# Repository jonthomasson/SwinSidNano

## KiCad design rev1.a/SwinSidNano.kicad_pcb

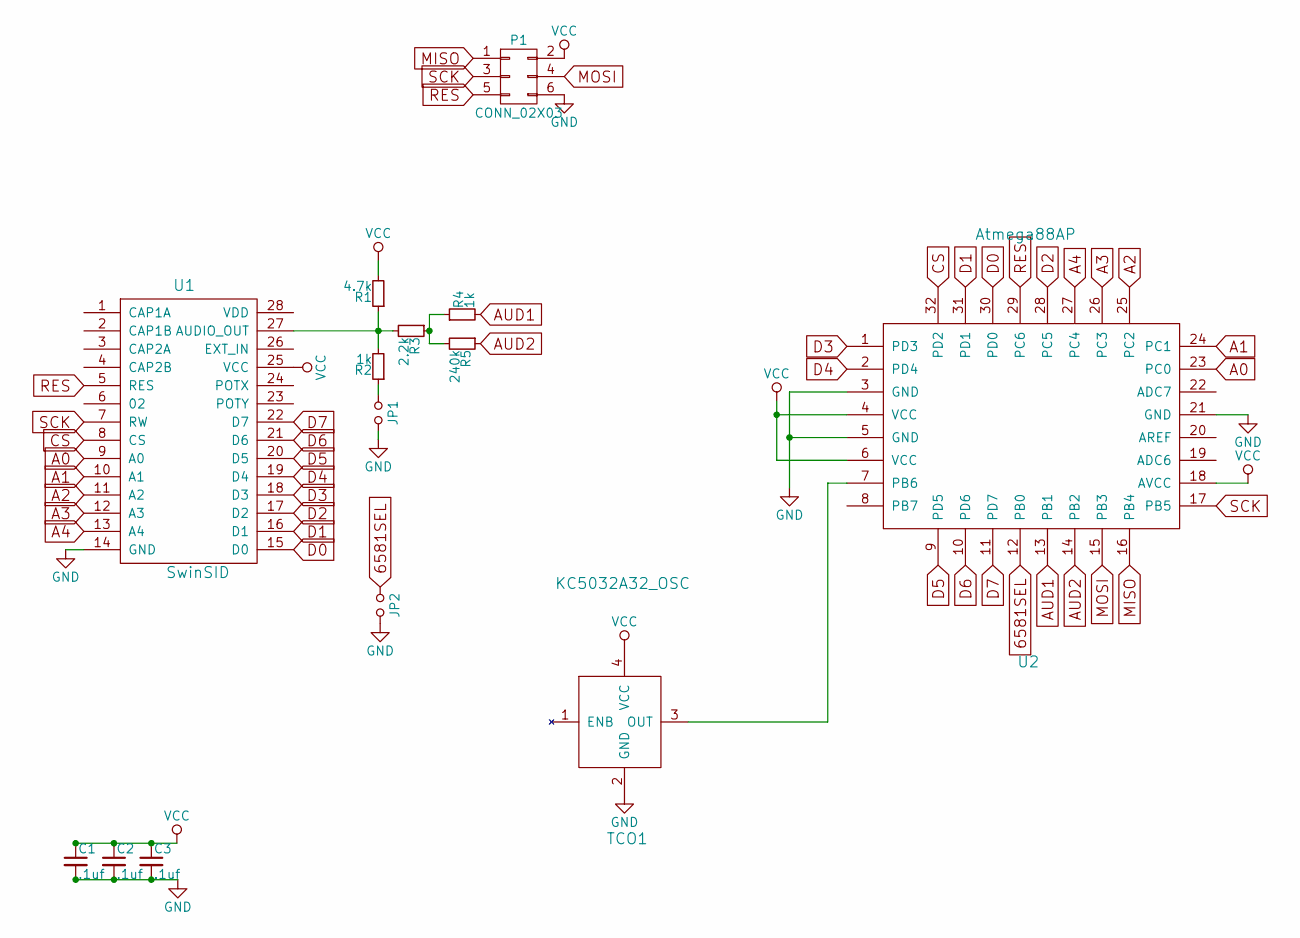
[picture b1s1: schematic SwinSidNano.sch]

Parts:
C1, C2, C3: .1uf; C_0805
JP1, JP2: Jumper_NO_Small; Pin_Header_Straight_1x02
P1: CONN_02X03; Pin_Header_Straight_2x03
R1: 4.7k; R_0805
R2, R4: 1k; R_0805
R3: 2.2k; R_0805
R5: 240k; R_0805
TCO1: KC5032A32_OSC; TCO-4
U1: SwinSID; DIP-28_W15.24mm
U2: Atmega88AP; TQFP-32_7x7mm_Pitch0.8mm

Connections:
6581SEL: JP2.1, U2.12 (PB0)
A0: U1.9 (A0), U2.23 (PC0)
A1: U1.10 (A1), U2.24 (PC1)
A2: U1.11 (A2), U2.25 (PC2)
A3: U1.12 (A3), U2.26 (PC3)
A4: U1.13 (A4), U2.27 (PC4)
AUD1: R4.2, U2.13 (PB1)
AUD2: R5.1, U2.14 (PB2)
CS: U1.8 (CS), U2.32 (PD2)
D0: U1.15 (D0), U2.30 (PD0)
D1: U1.16 (D1), U2.31 (PD1)
D2: U1.17 (D2), U2.28 (PC5)
D3: U1.18 (D3), U2.1 (PD3)
D4: U1.19 (D4), U2.2 (PD4)
D5: U1.20 (D5), U2.9 (PD5)
D6: U1.21 (D6), U2.10 (PD6)
D7: U1.22 (D7), U2.11 (PD7)
GND: C1.2, C2.2, C3.2, JP1.2, JP2.2, P1.6, TCO1.2 (GND), U1.14 (GND), U2.3 (GND), U2.5 (GND), U2.21 (GND); also elsewhere on the board
MISO: P1.1, U2.16 (PB4)
MOSI: P1.4, U2.15 (PB3)
unnamed: JP1.1, R2.1
unnamed: R1.1, R2.2, R3.2, U1.27 (AUDIO_OUT)
unnamed: R3.1, R4.1, R5.2
unnamed: TCO1.3 (OUT), U2.7 (PB6)
RES: P1.5, U1.5 (RES), U2.29 (PC6)
SCK: P1.3, U1.7 (RW), U2.17 (PB5)
VCC: C1.1, C2.1, C3.1, P1.2, R1.2, TCO1.4 (VCC), U1.25 (VCC), U2.4 (VCC), U2.6 (VCC), U2.18 (AVCC); also elsewhere on the board

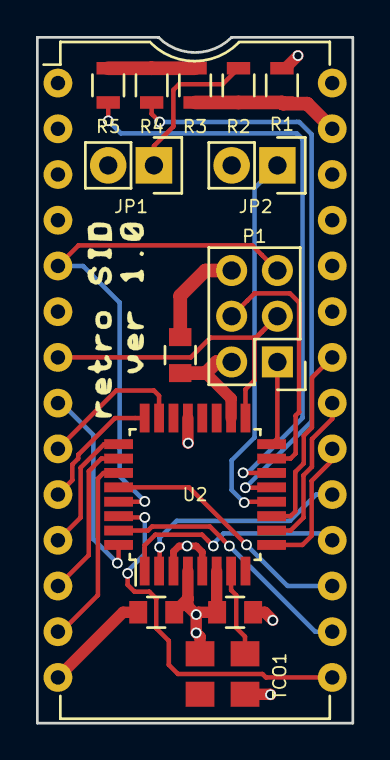
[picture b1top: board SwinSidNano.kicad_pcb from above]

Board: 4 copper layers, 17.5 x 38.1 mm, 14 parts (0 on the bottom side), 27 nets.

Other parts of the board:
C4: .1uf; C_0805

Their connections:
GND: C4.2; also elsewhere on the board
VCC: C4.1; also elsewhere on the board

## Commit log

2018-02-02 :boom::camel: Added .gitattributes & .gitignore files
